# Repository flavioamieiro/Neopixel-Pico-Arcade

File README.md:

The Neopixel Pico Arcade is a simple mini game with LEDs for a screen and
controlled by an NES controller.

It's built around the [RP2040
stamp](https://www.solder.party/rp2040_stamp_datasheet.pdf) designed by
@arturo182.

This source describes Open Hardware and is licensed under the CERN-OHL-S v2.
You may redistribute and modify this source and make products using it under
the terms of the [CERN-OHL-S v2](https://ohwr.org/cern_ohl_s_v2.txt).

Source location: https://github.com/flavioamieiro/Neopixel-Pico-Arcade

As per CERN-OHL-S v2 section 4, should You produce hardware based on this
source, You must where practicable maintain the Source Location visible on the
external case of the Gizmo or other products you make using this source.

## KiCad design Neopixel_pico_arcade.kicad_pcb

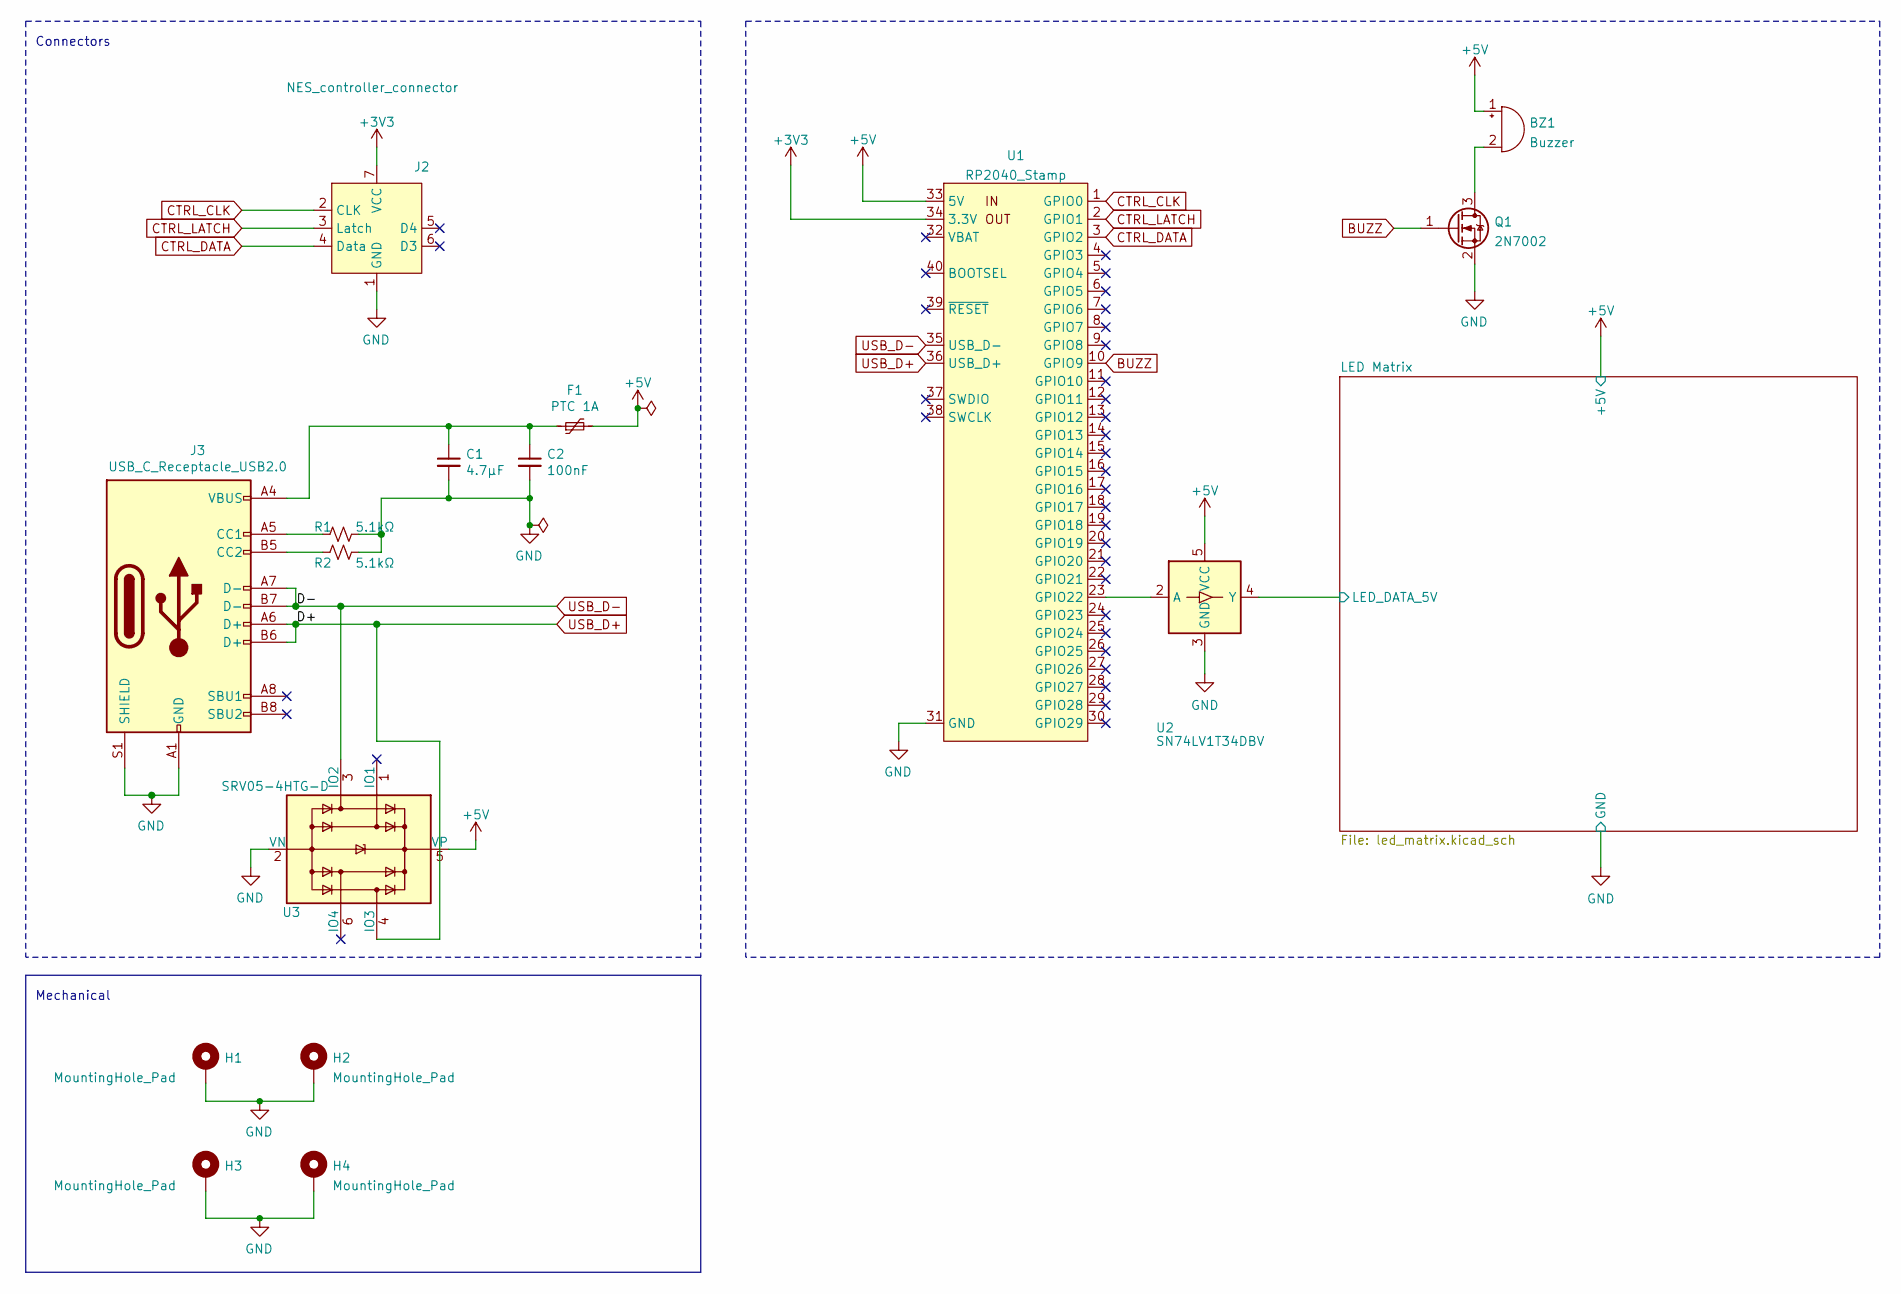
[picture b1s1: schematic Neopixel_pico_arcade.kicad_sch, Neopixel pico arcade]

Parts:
BZ1: Buzzer; MagneticBuzzer_CUI_CMT-8504-100-SMT
C1: 4.7µF; C_0805_2012Metric_Pad1.18x1.45mm_HandSolder
C2: 100nF; C_0805_2012Metric_Pad1.18x1.45mm_HandSolder
F1: PTC 1A; Belfuse_0ZCJ
H1, H2, H3, H4: MountingHole_Pad; MountingHole_3.2mm_M3_ISO7380_Pad_TopOnly
J2: NES_controller_connector; NES_Controller_connector
J3: USB_C_Receptacle_USB2.0; USB_C_Receptacle_USB_2_GTC_USB4105
Q1: 2N7002; SOT-23
R1, R2: 5.1kΩ; R_0805_2012Metric_Pad1.20x1.40mm_HandSolder
U1: RP2040_Stamp; RP2040_Stamp_SMD
U2: SN74LV1T34DBV; SOT-23-5
U3: SRV05-4HTG-D; SOT-23-6; MPN SRV05-4HTG-D

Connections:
+3V3: J2.7 (VCC), U1.34 (3.3V)
+5V: BZ1.1 (-), F1.2, U1.33 (5V), U2.5 (VCC), U3.5 (VP); also elsewhere on the board
/LED Matrix/LED_DATA_5V: U2.4 (Y); also elsewhere on the board
BUZZ: Q1.1 (G), U1.10 (GPIO9)
CTRL_CLK: J2.2 (CLK), U1.1 (GPIO0)
CTRL_DATA: J2.4 (Data), U1.3 (GPIO2)
CTRL_LATCH: J2.3 (Latch), U1.2 (GPIO1)
GND: C1.2, C2.2, H1.1, H2.1, H3.1, H4.1, J2.1 (GND), J3.A1 (GND), J3.A12 (GND), J3.B1 (GND), J3.B12 (GND), J3.S1 (SHIELD), Q1.2 (S), R1.2, R2.2, U1.31 (GND), U2.3 (GND), U3.2 (VN); also elsewhere on the board
unnamed: BZ1.2 (+), Q1.3 (D)
unnamed: C1.1, C2.1, F1.1, J3.A4 (VBUS), J3.A9 (VBUS), J3.B4 (VBUS), J3.B9 (VBUS)
unnamed: J3.A5 (CC1), R1.1
unnamed: J3.B5 (CC2), R2.1
unnamed: U1.23 (GPIO22), U2.2 (A)
USB_D+: J3.A6 (D+), J3.B6 (D+), U1.36 (USB_D+), U3.4 (IO3)
USB_D-: J3.A7 (D-), J3.B7 (D-), U1.35 (USB_D-), U3.3 (IO2)

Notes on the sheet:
Mechanical
Connectors

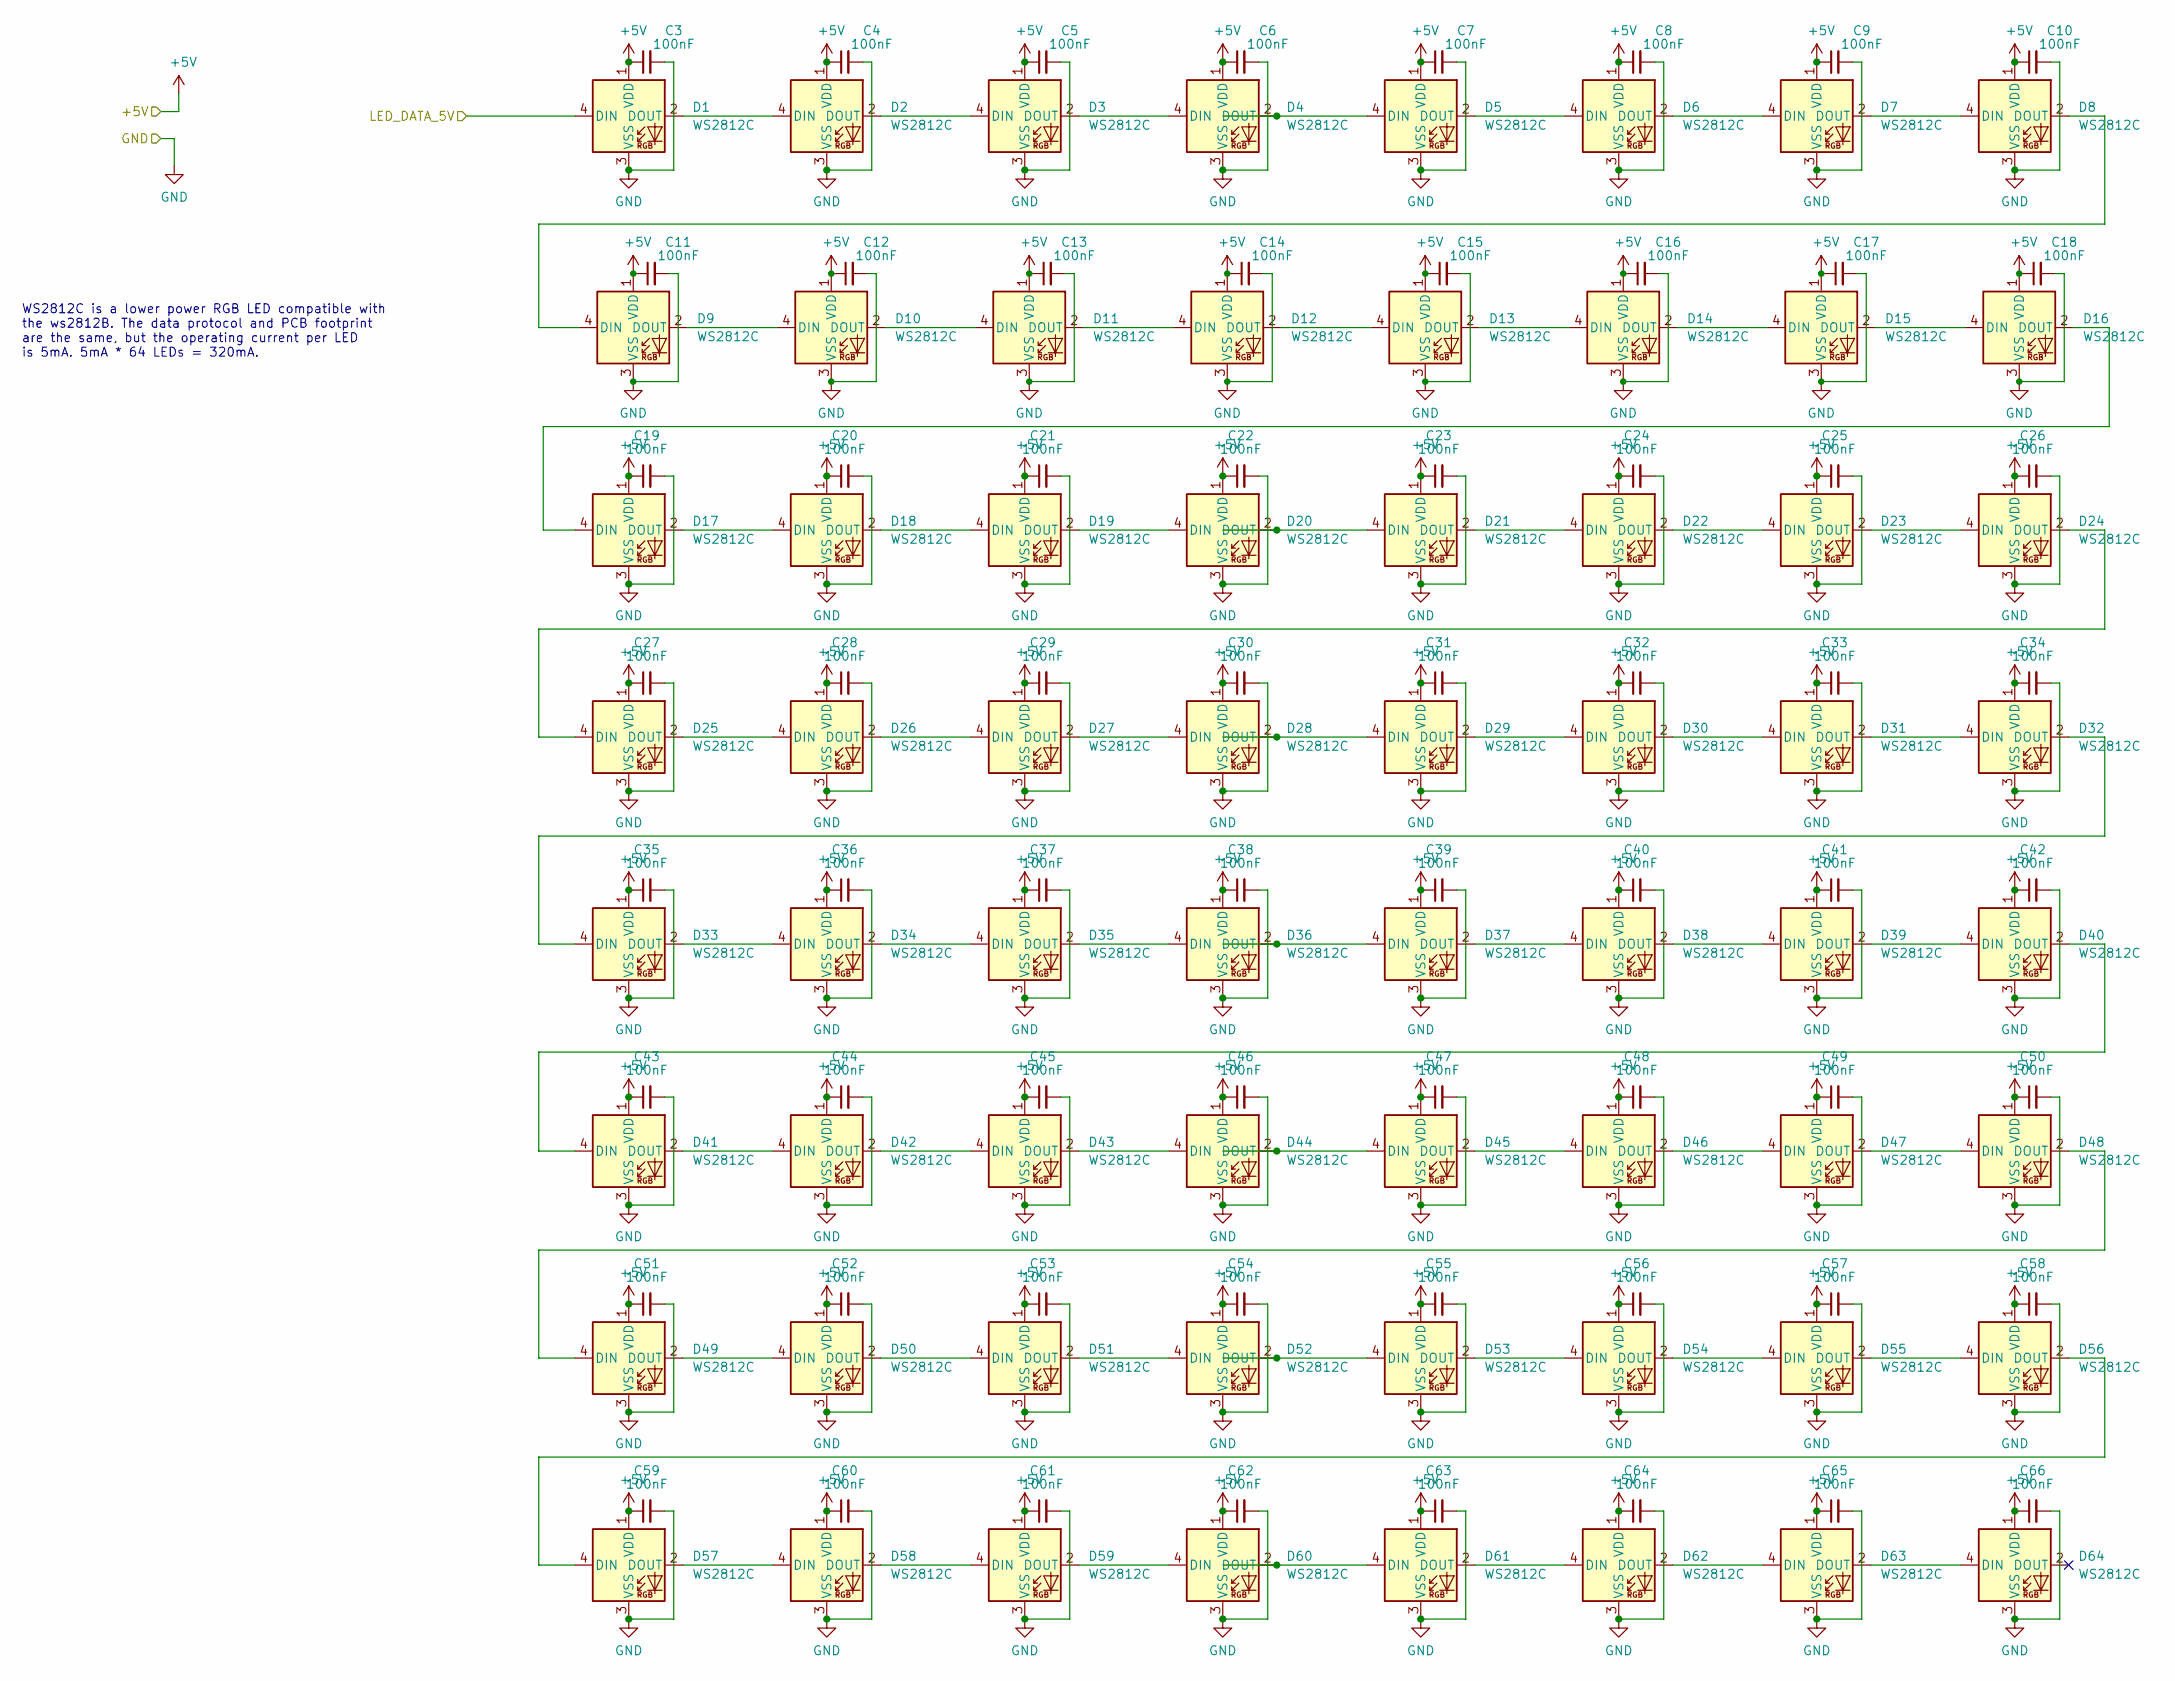
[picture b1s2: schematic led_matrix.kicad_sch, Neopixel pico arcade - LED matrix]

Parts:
C3, C4, C5, C6, C7, C8, C9, C10, C11, C12, C13, C14, C15, C16, C17, C18, C19, C20, C21, C22, C23, C24, C25, C26, C27, C28, C29, C30, C31, C32, C33, C34, C35, C36, C37, C38, C39, C40, C41, C42, C43, C44, C45, C46, C47, C48, C49, C50, C51, C52, C53, C54, C55, C56, C57, C58, C59, C60, C61, C62, C63, C64, C65, C66: 100nF; C_0805_hidden_silkscreen_2012Metric_Pad1.18x1.45mm_HandSold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; LCSC C49678
D1, D2, D3, D4, D5, D6, D7, D8, D9, D10, D11, D12, D13, D14, D15, D16, D17, D18, D19, D20, D21, D22, D23, D24, D25, D26, D27, D28, D29, D30, D31, D32, D33, D34, D35, D36, D37, D38, D39, D40, D41, D42, D43, D44, D45, D46, D47, D48, D49, D50, D51, D52, D53, D54, D55, D56, D57, D58, D59, D60, D61, D62, D63, D64: WS2812C; LED_WS2812C_HIDDEN_SILKSCREEN_5.0x5.0mm_P3.2mm; LCSC C114587

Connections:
+5V: C3.1, C4.1, C5.1, C6.1, C7.1, C8.1, C9.1, C10.1, C11.1, C12.1, C13.1, C14.1, C15.1, C16.1, C17.1, C18.1, C19.1, C20.1, C21.1, C22.1, C23.1, C24.1, C25.1, C26.1, C27.1, C28.1, C29.1, C30.1, C31.1, C32.1, C33.1, C34.1, C35.1, C36.1, C37.1, C38.1, C39.1, C40.1, C41.1, C42.1, C43.1, C44.1, C45.1, C46.1, C47.1, C48.1, C49.1, C50.1, C51.1, C52.1, C53.1, C54.1, C55.1, C56.1, C57.1, C58.1, C59.1, C60.1, C61.1, C62.1, C63.1, C64.1, C65.1, C66.1, D1.1 (VDD), D2.1 (VDD), D3.1 (VDD), D4.1 (VDD), D5.1 (VDD), D6.1 (VDD), D7.1 (VDD), D8.1 (VDD), D9.1 (VDD), D10.1 (VDD), D11.1 (VDD), D12.1 (VDD), D13.1 (VDD), D14.1 (VDD), D15.1 (VDD), D16.1 (VDD), D17.1 (VDD), D18.1 (VDD), D19.1 (VDD), D20.1 (VDD), D21.1 (VDD), D22.1 (VDD), D23.1 (VDD), D24.1 (VDD), D25.1 (VDD), D26.1 (VDD), D27.1 (VDD), D28.1 (VDD), D29.1 (VDD), D30.1 (VDD), D31.1 (VDD), D32.1 (VDD), D33.1 (VDD), D34.1 (VDD), D35.1 (VDD), D36.1 (VDD), D37.1 (VDD), D38.1 (VDD), D39.1 (VDD), D40.1 (VDD), D41.1 (VDD), D42.1 (VDD), D43.1 (VDD), D44.1 (VDD), D45.1 (VDD), D46.1 (VDD), D47.1 (VDD), D48.1 (VDD), D49.1 (VDD), D50.1 (VDD), D51.1 (VDD), D52.1 (VDD), D53.1 (VDD), D54.1 (VDD), D55.1 (VDD), D56.1 (VDD), D57.1 (VDD), D58.1 (VDD), D59.1 (VDD), D60.1 (VDD), D61.1 (VDD), D62.1 (VDD), D63.1 (VDD), D64.1 (VDD); also elsewhere on the board
/LED Matrix/LED_DATA_5V: D1.4 (DIN); also elsewhere on the board
GND: C3.2, C4.2, C5.2, C6.2, C7.2, C8.2, C9.2, C10.2, C11.2, C12.2, C13.2, C14.2, C15.2, C16.2, C17.2, C18.2, C19.2, C20.2, C21.2, C22.2, C23.2, C24.2, C25.2, C26.2, C27.2, C28.2, C29.2, C30.2, C31.2, C32.2, C33.2, C34.2, C35.2, C36.2, C37.2, C38.2, C39.2, C40.2, C41.2, C42.2, C43.2, C44.2, C45.2, C46.2, C47.2, C48.2, C49.2, C50.2, C51.2, C52.2, C53.2, C54.2, C55.2, C56.2, C57.2, C58.2, C59.2, C60.2, C61.2, C62.2, C63.2, C64.2, C65.2, C66.2, D1.3 (VSS), D2.3 (VSS), D3.3 (VSS), D4.3 (VSS), D5.3 (VSS), D6.3 (VSS), D7.3 (VSS), D8.3 (VSS), D9.3 (VSS), D10.3 (VSS), D11.3 (VSS), D12.3 (VSS), D13.3 (VSS), D14.3 (VSS), D15.3 (VSS), D16.3 (VSS), D17.3 (VSS), D18.3 (VSS), D19.3 (VSS), D20.3 (VSS), D21.3 (VSS), D22.3 (VSS), D23.3 (VSS), D24.3 (VSS), D25.3 (VSS), D26.3 (VSS), D27.3 (VSS), D28.3 (VSS), D29.3 (VSS), D30.3 (VSS), D31.3 (VSS), D32.3 (VSS), D33.3 (VSS), D34.3 (VSS), D35.3 (VSS), D36.3 (VSS), D37.3 (VSS), D38.3 (VSS), D39.3 (VSS), D40.3 (VSS), D41.3 (VSS), D42.3 (VSS), D43.3 (VSS), D44.3 (VSS), D45.3 (VSS), D46.3 (VSS), D47.3 (VSS), D48.3 (VSS), D49.3 (VSS), D50.3 (VSS), D51.3 (VSS), D52.3 (VSS), D53.3 (VSS), D54.3 (VSS), D55.3 (VSS), D56.3 (VSS), D57.3 (VSS), D58.3 (VSS), D59.3 (VSS), D60.3 (VSS), D61.3 (VSS), D62.3 (VSS), D63.3 (VSS), D64.3 (VSS); also elsewhere on the board
unnamed: D1.2 (DOUT), D2.4 (DIN)
unnamed: D2.2 (DOUT), D3.4 (DIN)
unnamed: D3.2 (DOUT), D4.4 (DIN)
unnamed: D4.2 (DOUT), D5.4 (DIN)
unnamed: D5.2 (DOUT), D6.4 (DIN)
unnamed: D6.2 (DOUT), D7.4 (DIN)
unnamed: D7.2 (DOUT), D8.4 (DIN)
unnamed: D8.2 (DOUT), D9.4 (DIN)
unnamed: D10.2 (DOUT), D11.4 (DIN)
unnamed: D9.2 (DOUT), D10.4 (DIN)
unnamed: D11.2 (DOUT), D12.4 (DIN)
unnamed: D12.2 (DOUT), D13.4 (DIN)
unnamed: D13.2 (DOUT), D14.4 (DIN)
unnamed: D14.2 (DOUT), D15.4 (DIN)
unnamed: D15.2 (DOUT), D16.4 (DIN)
unnamed: D16.2 (DOUT), D17.4 (DIN)
unnamed: D17.2 (DOUT), D18.4 (DIN)
unnamed: D18.2 (DOUT), D19.4 (DIN)
unnamed: D19.2 (DOUT), D20.4 (DIN)
unnamed: D20.2 (DOUT), D21.4 (DIN)
unnamed: D21.2 (DOUT), D22.4 (DIN)
unnamed: D22.2 (DOUT), D23.4 (DIN)
unnamed: D23.2 (DOUT), D24.4 (DIN)
unnamed: D24.2 (DOUT), D25.4 (DIN)
unnamed: D25.2 (DOUT), D26.4 (DIN)
unnamed: D26.2 (DOUT), D27.4 (DIN)
unnamed: D27.2 (DOUT), D28.4 (DIN)
unnamed: D28.2 (DOUT), D29.4 (DIN)
unnamed: D29.2 (DOUT), D30.4 (DIN)
unnamed: D30.2 (DOUT), D31.4 (DIN)
unnamed: D31.2 (DOUT), D32.4 (DIN)
unnamed: D32.2 (DOUT), D33.4 (DIN)
unnamed: D33.2 (DOUT), D34.4 (DIN)
unnamed: D34.2 (DOUT), D35.4 (DIN)
unnamed: D35.2 (DOUT), D36.4 (DIN)
unnamed: D36.2 (DOUT), D37.4 (DIN)
unnamed: D37.2 (DOUT), D38.4 (DIN)
unnamed: D38.2 (DOUT), D39.4 (DIN)
unnamed: D39.2 (DOUT), D40.4 (DIN)
unnamed: D40.2 (DOUT), D41.4 (DIN)
unnamed: D41.2 (DOUT), D42.4 (DIN)
unnamed: D42.2 (DOUT), D43.4 (DIN)
unnamed: D43.2 (DOUT), D44.4 (DIN)
unnamed: D44.2 (DOUT), D45.4 (DIN)
unnamed: D45.2 (DOUT), D46.4 (DIN)
unnamed: D46.2 (DOUT), D47.4 (DIN)
unnamed: D47.2 (DOUT), D48.4 (DIN)
unnamed: D48.2 (DOUT), D49.4 (DIN)
unnamed: D49.2 (DOUT), D50.4 (DIN)
unnamed: D50.2 (DOUT), D51.4 (DIN)
unnamed: D51.2 (DOUT), D52.4 (DIN)
unnamed: D52.2 (DOUT), D53.4 (DIN)
unnamed: D53.2 (DOUT), D54.4 (DIN)
unnamed: D54.2 (DOUT), D55.4 (DIN)
unnamed: D55.2 (DOUT), D56.4 (DIN)
unnamed: D56.2 (DOUT), D57.4 (DIN)
unnamed: D57.2 (DOUT), D58.4 (DIN)
unnamed: D58.2 (DOUT), D59.4 (DIN)
unnamed: D59.2 (DOUT), D60.4 (DIN)
unnamed: D60.2 (DOUT), D61.4 (DIN)
unnamed: D61.2 (DOUT), D62.4 (DIN)
unnamed: D62.2 (DOUT), D63.4 (DIN)
unnamed: D63.2 (DOUT), D64.4 (DIN)

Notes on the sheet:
WS2812C is a lower power RGB LED compatible with the ws2812B. The data protocol and PCB footprint are the same, but the operating current per LED is 5mA. 5mA * 64 LEDs = 320mA.

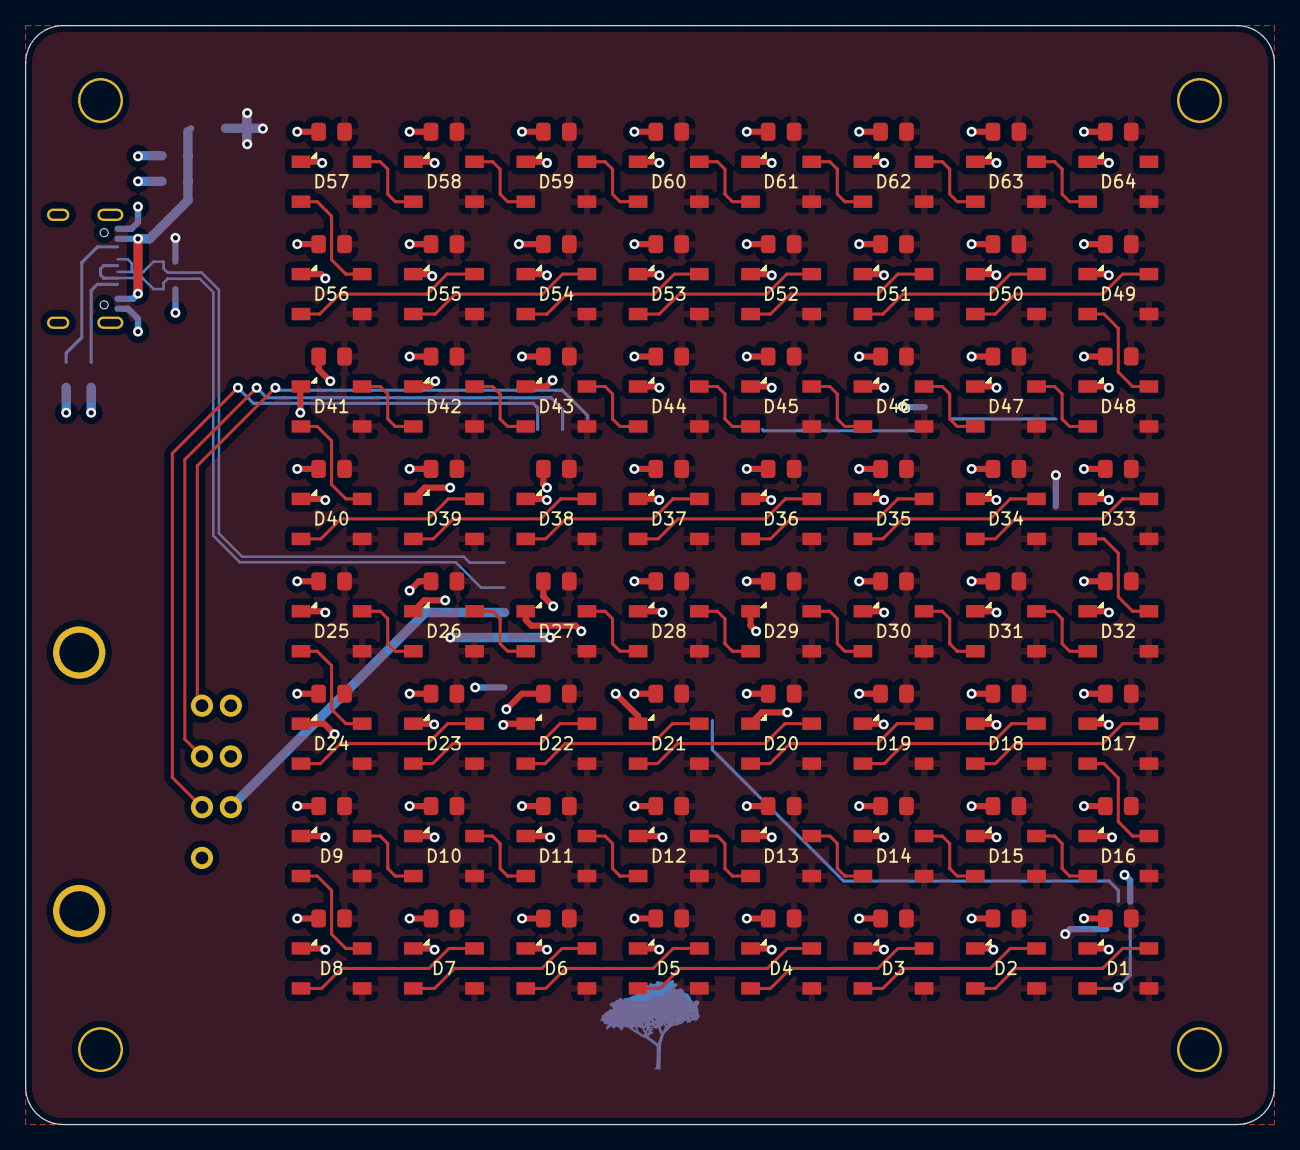
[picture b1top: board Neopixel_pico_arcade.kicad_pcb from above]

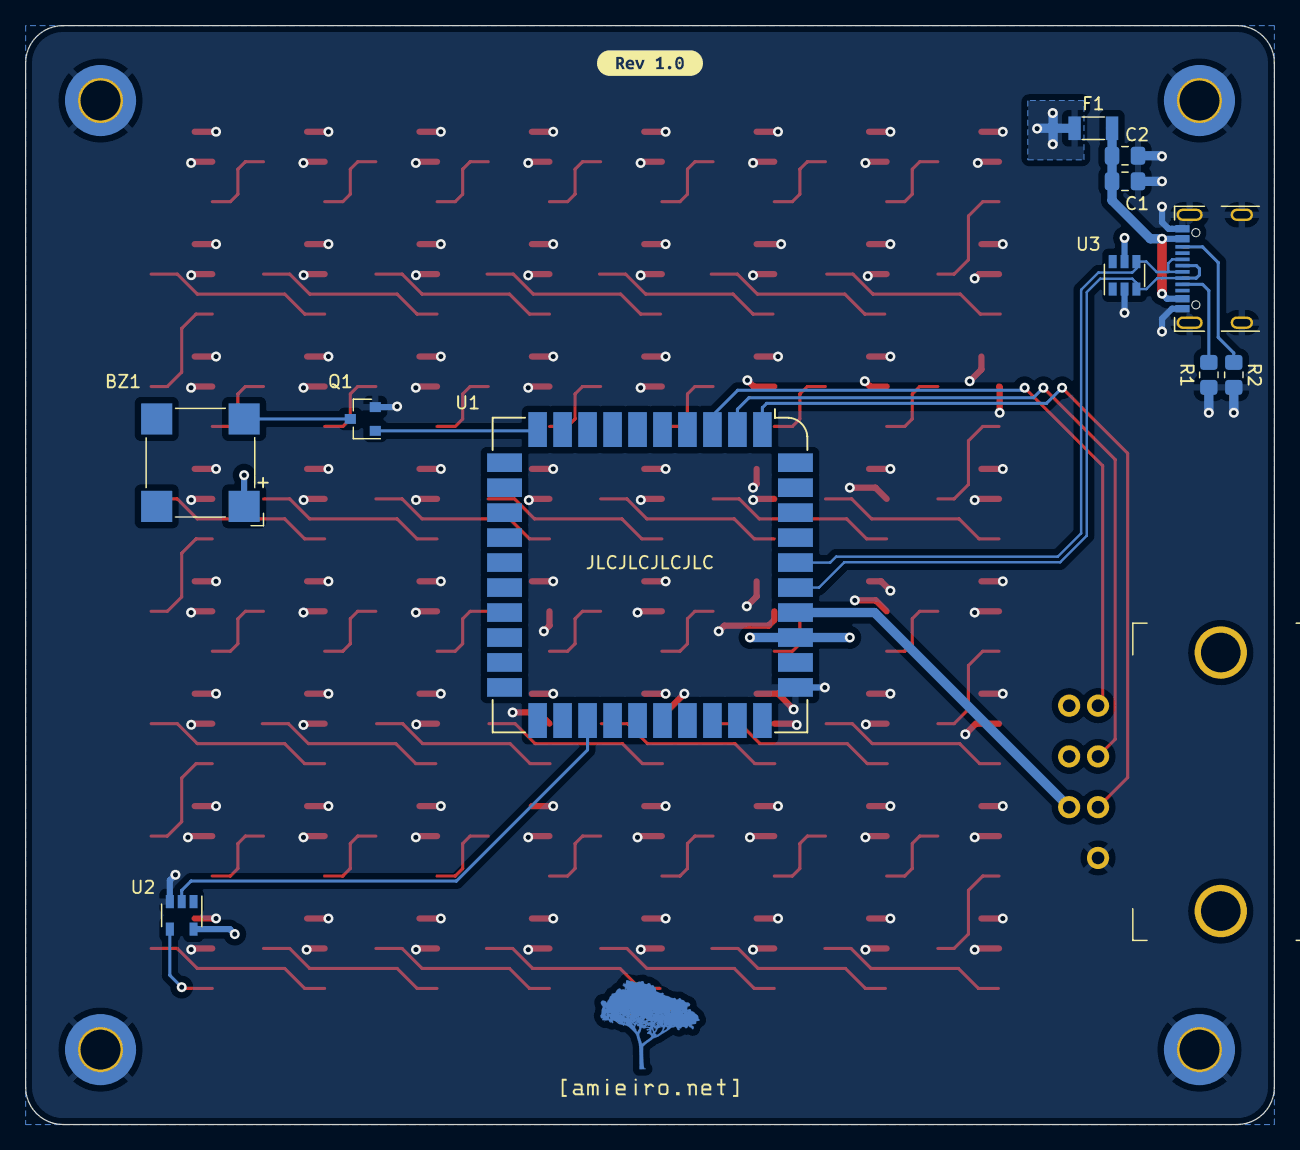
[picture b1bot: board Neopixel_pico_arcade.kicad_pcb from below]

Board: 4 copper layers, 100.0 x 88.0 mm, 147 parts (17 on the bottom side), 78 nets.

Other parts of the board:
Ref**: Val**; url_bsilks
Ref**#2: Val**; ipe_logo
kibuzzard-615E1A5A: G***; kibuzzard-615E1A5A

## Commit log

2021-09-17 Initial commit with incomplete schematics
    This commit includes the start point for the schematics (still missing
    mainly the boost converter block) and the schematic symbol and footprint
    for the RP2040 stamp[1].
    [1]: https://github.com/solderparty/rp2040_stamp_footprints
2021-09-18 Removes boost converter placeholder since it won't be possible to use it
    The stamp can only provide 500mA@3.3v, which gives us 1.65W. Assuming a
    85% efficiency of the boost regulator, that would give us 1.4W on the
    output, or 280mA@5V. We need 320mA to run the 64 WS2812C, so it doesn't
    seem to be possible to run these from a LiPO battery unless we rely on
    the software never running all the LEDs at full brightness, but that
    doesn't seem like a reliable option.
2021-09-19 Renames the project to Neopixel pico arcade
2021-09-19 Adds bulk capacitance for USB power
    USB devices should be limited to at most 10µF capacitance to keep inrush
    current under the specified limits.
2021-09-21 Adds jumpers to latch and clock lines to make rework easier
    I've switched those two pins a few times already during prototyping.
    With the normally closed jumpers it will be easier to swap them if I
    make a mistake while laying out the board.
2021-09-21 Adds a buzzer to the schematics
    We needed a way to generate some kind of annoying sound :)
2021-09-29 Annotates components on schematics
2021-09-29 Align elements to grid
2021-09-29 Changes +5v symbols
    These were copied from another project and Kicad included references to
    that library.
2021-09-29 Fixes ERC errors on top level sheet
2021-09-29 Fixes ERC errors in the LED matrix schematics
2021-09-29 Adds sym-lib-table that was missing
2021-09-29 Associates most components with footprints
    We're still missing the NES controller connector footprint.
2021-09-29 Adds custom schematic symbol for NES controller connector
2021-09-30 Adds footprint for the NES controller connector
2021-09-30 Adds 3d model for NES connector
    Derived from a .stl file downloaded from https://www.thingiverse.com/thing:1753655
2021-09-30 Associates capacitors to the correct footprint
2021-09-30 Reassociates RP2040 stamp to the footprint
2021-09-30 Fixes RP2040 3d model path
    This was wrong after Iimported the files.
2021-10-03 Adds footprint for GTC USB4105 USB type C connector
    This connector is for USB2.0 and power delivery only.
    Datasheet is available at https://gct.co/files/specs/usb4105-spec.pdf
    and drawings at https://gct.co/files/drawings/usb4105.pdf
2021-10-03 Adds project name and revision to schematics
2021-10-03 Adds kicad_prl to gitignore
    This file stores local settings[1], so it should not be tracked by git.
    [1]: https://forum.kicad.info/t/new-project-file-format/23705
2021-10-03 Adds mounting holes to schematics
    These are connected to ground, but will have pads only on once the
    bottom so the exposed pad on top doesn't interfere with the face where
    the LEDs are.
2021-10-03 Adds basic PCB file with board outline
2021-10-03 Switches SWD connector to SDM pin headers
2021-10-03 Moves bottom side components roughly into place
    The NES connector will still need to move to make space for the LEDs.
    This probably means the PCB will need to grow.
2021-10-03 Arranges LEDs in an ordered matrix
2021-10-03 Arranges capacitors in the LED matrix
2021-10-03 Uses a copy of the built-in WS2812B footprint but with hidden silkscreen
    Since this will be the screen, it's better to have no visible silkscreen.
2021-10-03 Adds a copy of the built-in 0805 capacitor footprint with no silkscreen
    For the same reason we hid the LED silkscreen.
2021-10-03 Fixes PCB thickness
    When changing to a 4-layer PCB in the setup it didn't adapt the overall
    thickness to 1.6mm.
2021-10-03 Adjusts LED matrix placement
    Because of the NES connector and it's through hole leads it's really
    hard to keep it symmetric while keeping it under 100mm x 100mm*. The
    solution I found is to keep the spacing between the LEDs and the edges
    the same in all but the side where the connectors are. This would
    probably be better in the bottom, but then the cables would have nowhere
    to exit from.
2021-10-03 Fixes LED ordering in the matrix
    After routing some of the LED data pins, I noticed some of the last rows
    were wrong.
2021-10-03 Routes data pins between the LEDs
2021-10-03 First rough pass at routing
    Everything can be improved a lot, and I don't have vias to ground on the
    top layer. The 3v3 line to the controller is also missing.
2021-10-05 Routes ground for LEDs and their decoupling capacitors
2021-10-05 Changes positions of the controller and USB connector
    This makes it easier to route the USB signal and also makes more sense
    since the NES connector and cable are pretty heavy and will probably be
    better bellow.
2021-10-05 Removes SWD header
    We will very likely not need it anyways since we have a USB connection
    for programming.
2021-10-05 Removes jumpers from schematics
    If we mix up clock and latch we can swap them in software
2021-10-05 Reroutes NES controler lines
2021-10-05 Fixes pad entries for USB lines in TVS diodes
2021-10-05 Reorganizes power traces around USB connector
2021-10-05 Reorganizes some of the silkscreen designators
2021-10-06 Reroutes NES controller data lines
2021-10-06 Fixes most DRC errors and warnings
    There are still a few errors related to the USB-C connector footprint.
2021-10-06 Reorganizes data and power lines for NES controller
2021-10-06 Adds logo footprint to the board
2021-10-06 Adds revision number (1.0) and JLCPCB order number placeholder
2021-10-12 Adds interactive BOM generated by InteractiveHtmlBom
    https://github.com/openscopeproject/InteractiveHtmlBom
2021-10-17 Adds license information
2021-10-17 Adds PCB 3D renders and Schematics PDF to the repo
2021-10-17 Removes footprint for NES controller since it's completely broken
2021-10-17 Fixes image links in the README file
